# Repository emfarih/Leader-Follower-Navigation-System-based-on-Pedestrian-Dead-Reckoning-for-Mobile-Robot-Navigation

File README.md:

# Leader-Follower-Navigation-System-based-on-Pedestrian-Dead-Reckoning-for-Mobile-Robot-Navigation

This Repo contains full code of my thesis entitled Leader-Follower-Navigation-System-based-on-Pedestrian-Dead-Reckoning-for-Mobile-Robot-Navigation.

You can read this as paper on https://ieeexplore.ieee.org/document/8937138

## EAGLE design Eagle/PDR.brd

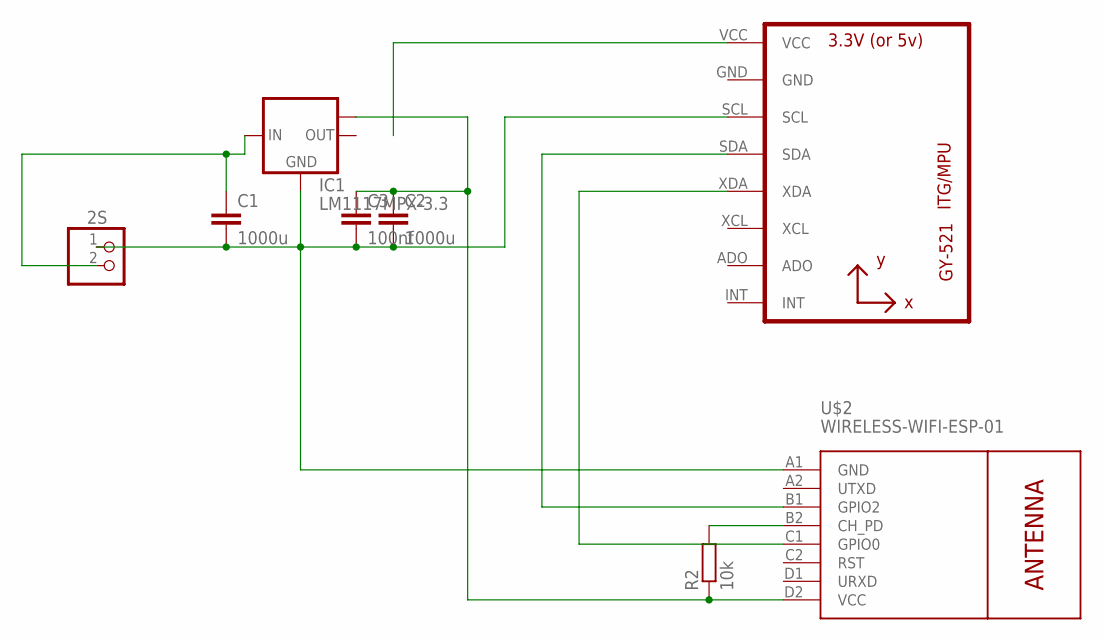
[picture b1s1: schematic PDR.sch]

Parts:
2S: PINHD-1X2; 1X02
C1, C2: 1000u; C2.5-2
C3: 100nf; C2.5-2
GY-91: GY-521MPU6050; GY-521
IC1: LM1117MPX-3.3; SOT223
R2: 10k; 0204/7
U$2: WIRELESS-WIFI-ESP-01

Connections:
unnamed: 2S.1, C1.2, C2.2, C3.2, GY-91.SCL, IC1.1 (GND), U$2.A1 (GND)
unnamed: 2S.2, C1.1, IC1.3 (IN)
unnamed: C2.1, C3.1, IC1.TAB (OUT1), R2.1, U$2.D2 (VCC)
unnamed: GY-91.SDA, U$2.B1 (GPIO2)
unnamed: GY-91.XDA, U$2.C1 (GPIO0)
unnamed: R2.2, U$2.B2 (CH_PD)

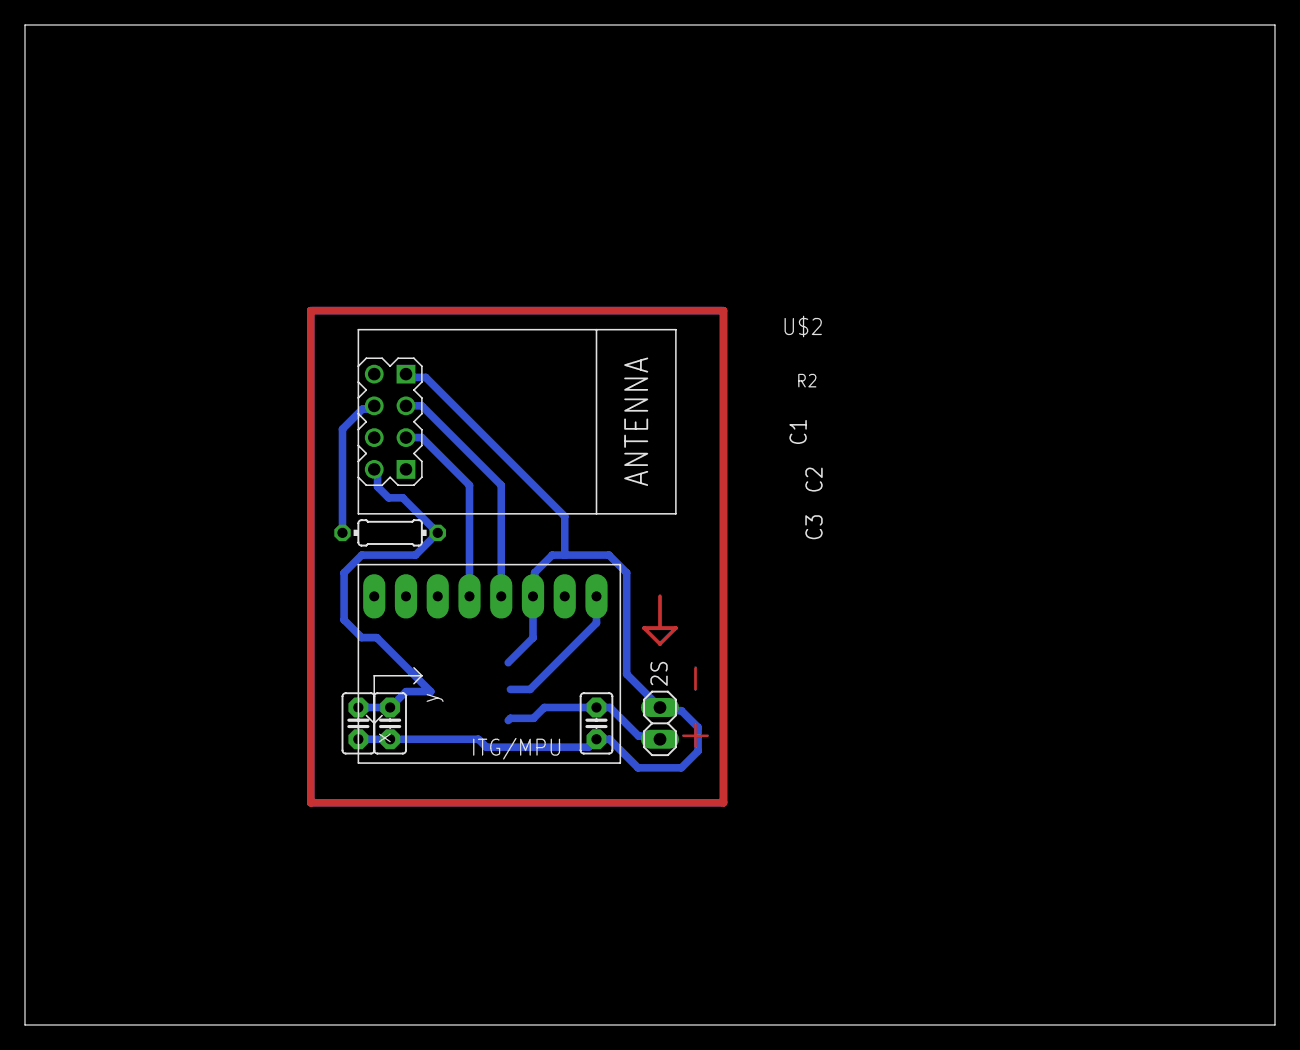
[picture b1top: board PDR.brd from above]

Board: 2 copper layers, 100.0 x 80.0 mm, 8 parts (1 on the bottom side), 6 nets.

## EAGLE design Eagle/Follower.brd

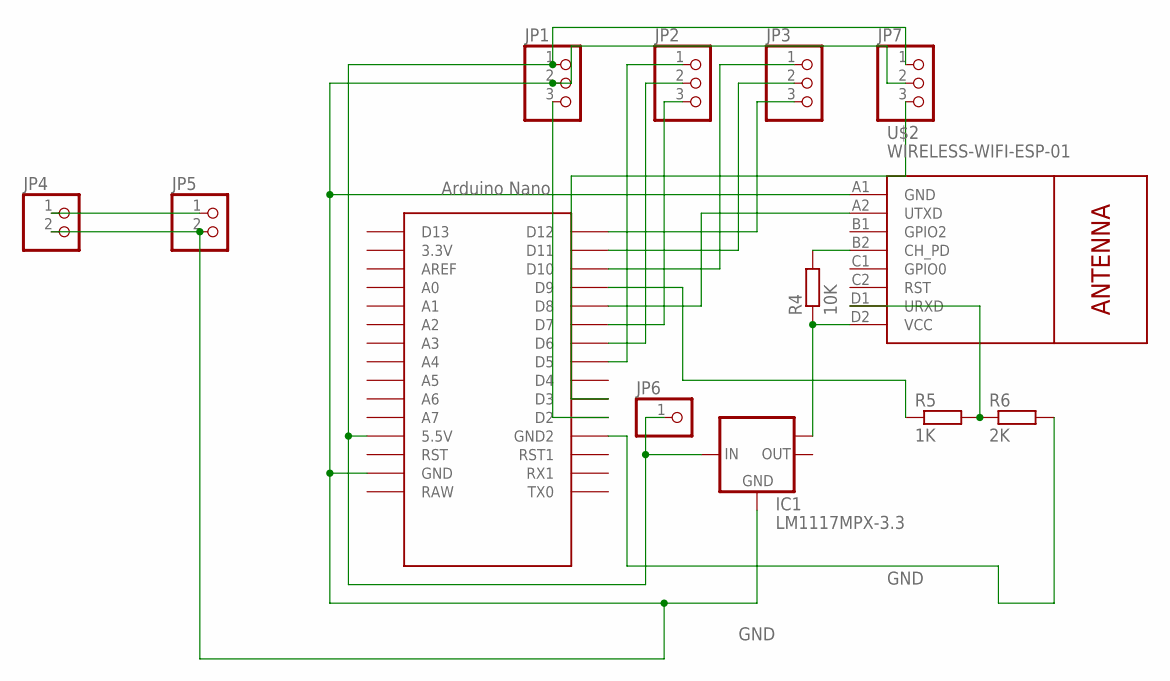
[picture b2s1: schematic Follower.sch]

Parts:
IC1: LM1117MPX-3.3; SOT223
JP1, JP2, JP3, JP7: PINHD-1X3; 1X03
JP4, JP5: PINHD-1X2; 1X02
JP6: PINHD-1X1; 1X01
R4: 10K; 0207/10
R5: 1K; 0207/10
R6: 2K; 0207/10
U$1: NANO
U$2: WIRELESS-WIFI-ESP-01

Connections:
7.4V: JP4.1, JP5.1
GND: IC1.1 (GND), JP1.2, JP4.2, JP5.2, JP7.2, R6.2, U$1.GND, U$1.GND1 (GND2), U$2.A1 (GND)
unnamed: IC1.3 (IN), JP1.1, JP6.1, JP7.1, U$1.5V (5.5V)
unnamed: U$1.D8, U$2.A2 (UTXD)
unnamed: R4.2, U$2.B2 (CH_PD)
unnamed: IC1.TAB (OUT1), R4.1, U$2.D2 (VCC)
unnamed: R5.1, U$1.D9
unnamed: R5.2, R6.1, U$2.D1 (URXD)
unnamed: JP2.1, U$1.D5
unnamed: JP2.2, U$1.D6
unnamed: JP2.3, U$1.D7
unnamed: JP3.1, U$1.D10
unnamed: JP3.2, U$1.D11
unnamed: JP3.3, U$1.D12
unnamed: JP1.3, U$1.D2
unnamed: JP7.3, U$1.D3

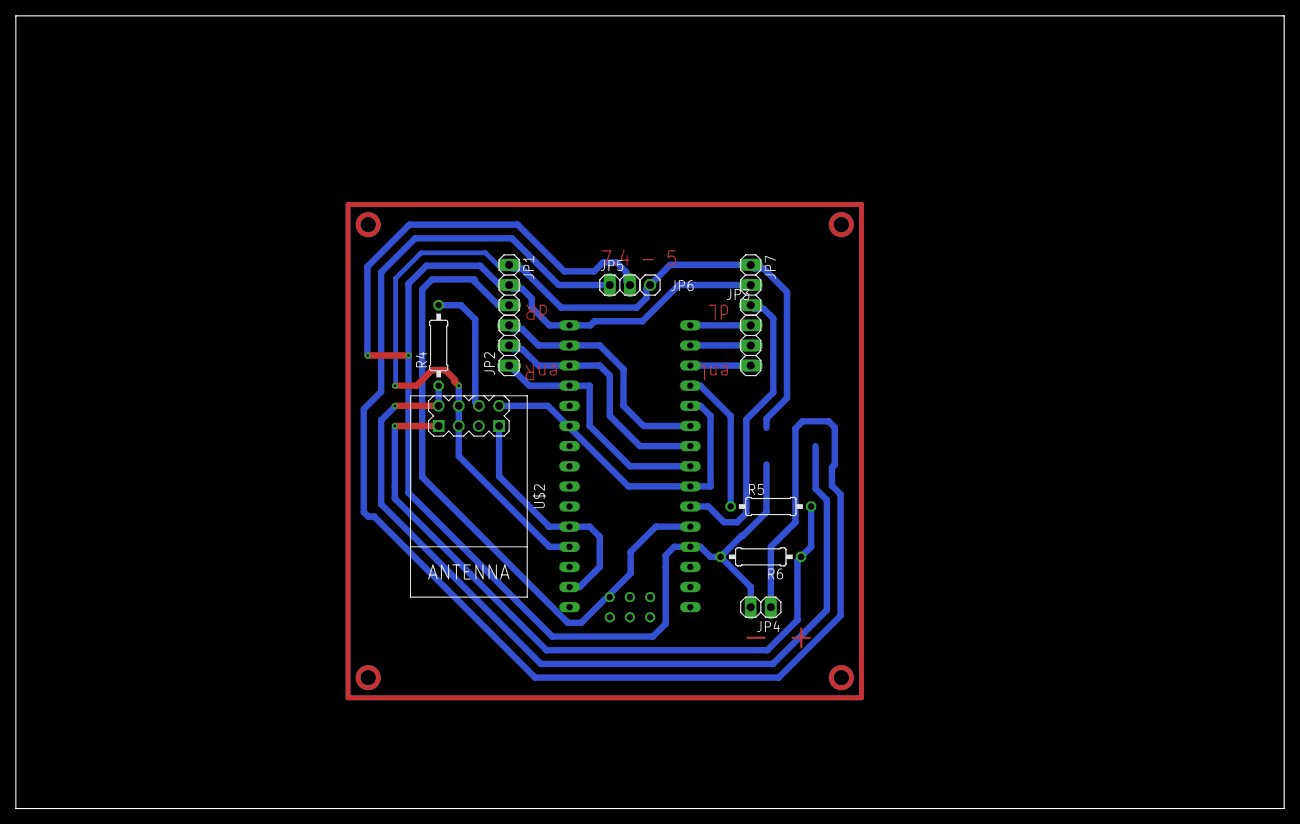
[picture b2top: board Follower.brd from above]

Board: 2 copper layers, 160.0 x 100.0 mm, 13 parts (1 on the bottom side), 16 nets.

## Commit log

2019-07-24 First Commit of Android App as Server, Controller, and Processor
2019-07-24 First Commit of PCB Eagle Designs
2019-07-24 First Commit of Arduino Based Scripts
2019-07-24 First Commit of Matlab Scripts
2019-07-24 First Commit of Python Scripts

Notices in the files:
parts and their libraries:
diy-modules: Released under the Creative Commons Attribution 4.0 International License: http://creativecommons.org/licenses/by/4.0
